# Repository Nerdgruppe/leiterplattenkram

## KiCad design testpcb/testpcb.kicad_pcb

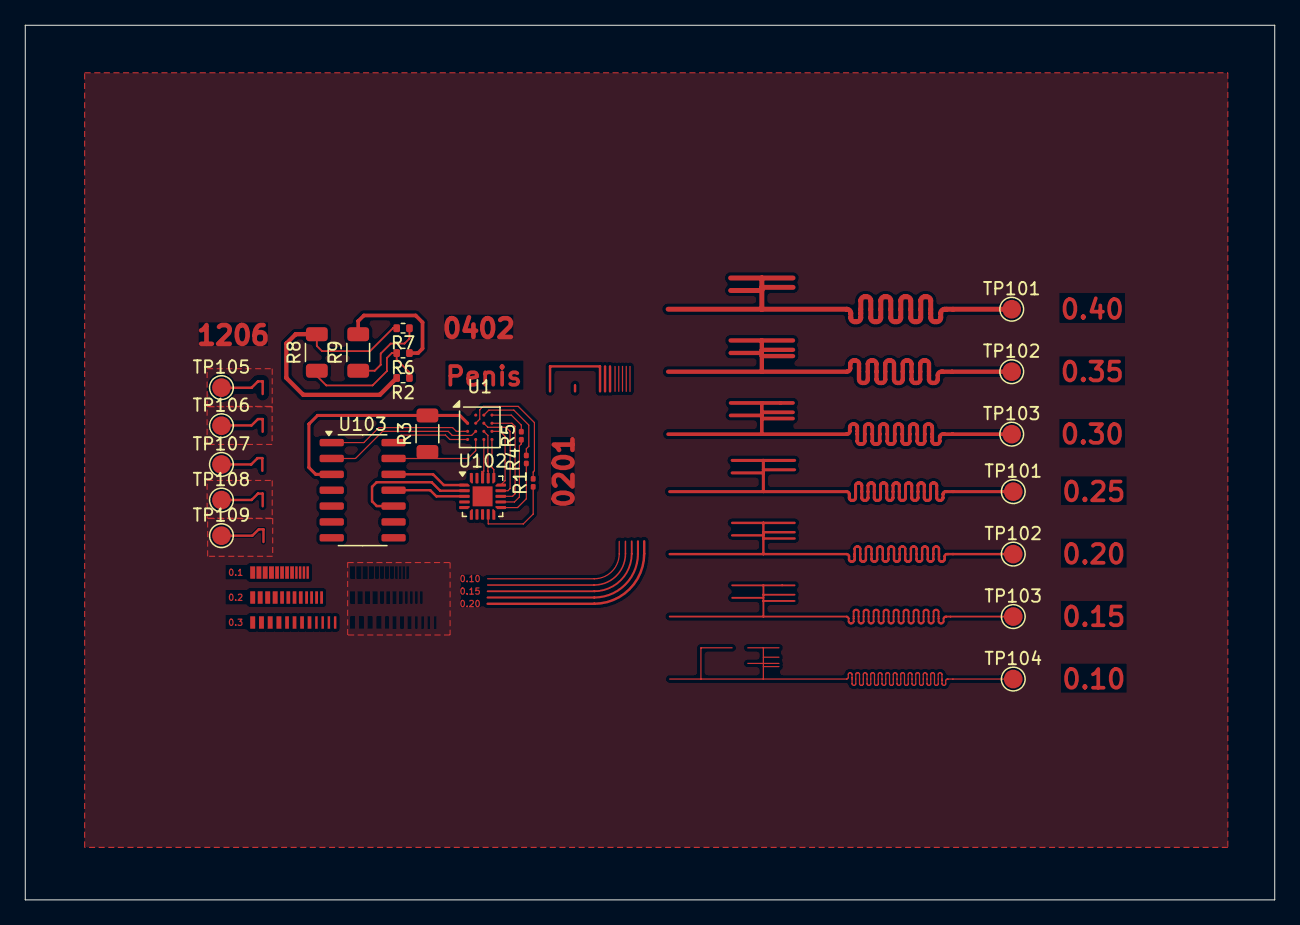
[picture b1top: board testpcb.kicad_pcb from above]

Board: 2 copper layers, 100.0 x 70.0 mm, 24 parts (0 on the bottom side), 23 nets.

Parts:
R1, R4, R5: R; R_0201_0603Metric
R2, R6, R7: R; R_0402_1005Metric
R3, R8, R9: R; R_1206_3216Metric
TP101, TP101#2, TP102, TP102#2, TP103, TP103#2, TP104, TP105, TP106, TP107, TP108, TP109: TestPoint; TestPoint_Pad_D1.5mm
U1: ATtiny20-CC; UFBGA-15_3.0x3.0mm_Layout4x4_P0.65mm
U102: ATtiny20-MM; QFN-20-1EP_3x3mm_P0.45mm_EP1.6x1.6mm
U103: ATtiny20-SS; SOIC-14_3.9x8.7mm_P1.27mm

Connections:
/Netze BW: TP103.1, TP103#2.1
/Telekom: TP101.1, TP101#2.1
/Vodafone: TP102.1, TP102#2.1
/testkringel_links: TP105.1, TP106.1, TP107.1, TP108.1, TP109.1
unnamed: U1.D1 (PA0), U103.14 (GND)
unnamed: U1.C3 (PA1), U102.17 (PA5)
unnamed: U1.C2 (PA2), U103.2 (PB0)
unnamed: U1.C1 (PA3), U103.1 (VCC)
unnamed: R3.2, U1.B1 (PA4), U103.3 (PB1)
unnamed: R3.1, U1.A2 (PA5), U1.D2 (GND), U1.D3 (GND), U102.8 (GND), U102.21 (GND), U103.13 (PA0)
unnamed: R4.2, U1.A3 (PA6)
unnamed: R1.2, U1.B2 (PA7)
unnamed: U1.C4 (PB0), U102.15 (PA7)
unnamed: U1.B3 (PB1), U102.14 (PB2)
unnamed: R5.2, U1.A4 (PB2)
unnamed: U1.D4 (VCC), U102.16 (PA6)
unnamed: U1.B4 (~RESET/PB3), U102.13 (~RESET/PB3)
unnamed: U102.3 (PA2), U103.11 (PA2)
unnamed: U102.2 (PA3), U103.10 (PA3)
unnamed: U102.1 (PA4), U103.12 (PA1)
unnamed: R4.1, U102.11 (PB0)
unnamed: R5.1, U102.12 (PB1)
unnamed: R1.1, U102.9 (VCC)

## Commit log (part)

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2025-10-17 sliced files testpcb
2025-10-17 Create blank
2025-10-17 Add files via upload
    modified files by @ikskuh with first antialias/greylevel compensation experiment
2025-10-17 Rename testpcb.pm4n to slicer/testpcb.pm4n
2025-10-17 Rename testpcb.pwscene to slicer/testpcb.pwscene
2025-10-19 Checks in Cameraserver
2025-10-20 designed pcb holder
2025-10-23 Uploads experimental scripts for autostitching tool
2025-10-23 Adds draft design for pcbholder
2025-10-23 Improves pcbholder design
2025-10-25 added more printfiles and print test
2025-10-25 added new file: hase pcbhalter test file (only testing print parameters with a low height); changed the bedcleaner to have a high lift distance
2025-10-26 saving work
2025-10-26 new version of test file
2025-11-07 next version of full part, with new print orientation and support
2025-11-07 VacBed/Xq.V1.1
2025-12-02 Initial commit of EtchMaster: Basic Web UI
2025-12-18 nächste testplatine
2026-05-17 Add configuration for PlatinenFooBurner ESP32
2026-05-23 Add CAD Daten für PlatinenÄtzhalter, AnsaugGrobfilter, Sprtzdüse
2026-06-06 Update mit Spülung und Ätzzeit
